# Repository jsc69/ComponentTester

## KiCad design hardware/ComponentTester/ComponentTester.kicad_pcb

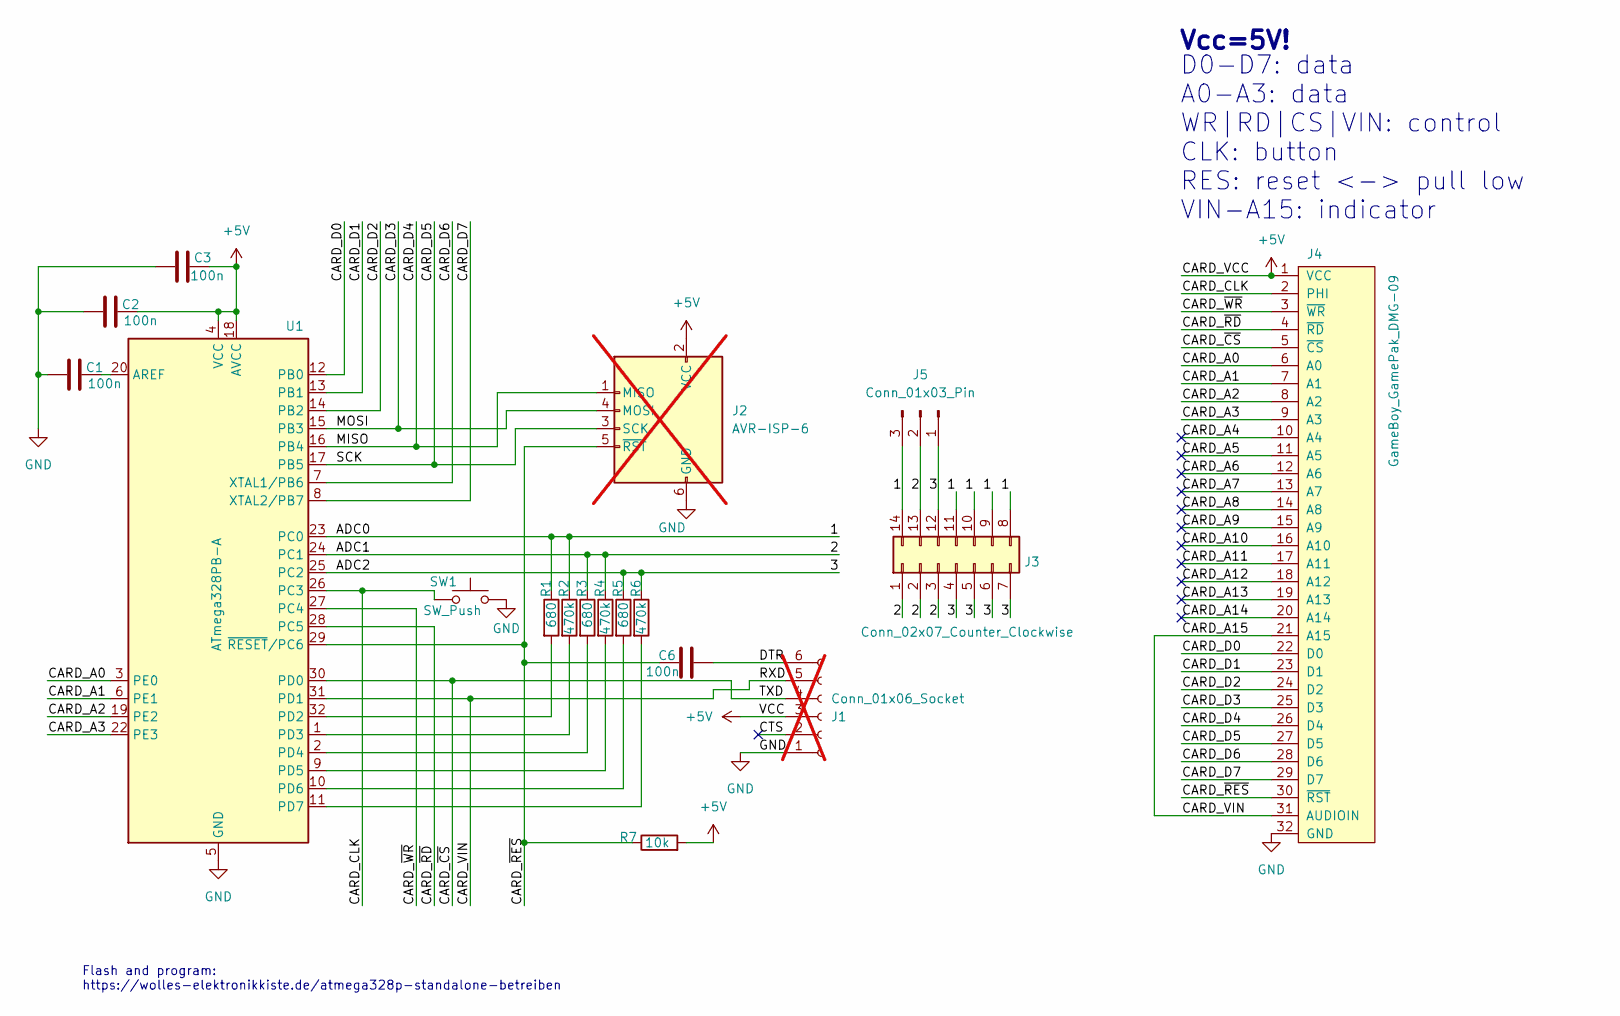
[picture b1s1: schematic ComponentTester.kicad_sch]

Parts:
C1, C2, C3, C6: 100n; C_0805_2012Metric
J1: Conn_01x06_Socket; PinHeader_1x06_P2.54mm_Vertical; not fitted
J2: AVR-ISP-6; PinHeader_2x03_P2.54mm_Vertical; not fitted
J3: Conn_02x07_Counter_Clockwise; DIP_Socket-14_W4.3mm_W5.08mm_W7.62mm_W10.16mm_W10.9mm_3M_21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
J4: GameBoy_GamePak_DMG-09; GameBoy_GamePak_DMG-09_P1.50mm_Edge
J5: Conn_01x03_Pin; Component_Testpad
R1, R3, R5: 680; R_0805_2012Metric
R2, R4, R6: 470k; R_0805_2012Metric
R7: 10k; R_0805_2012Metric
SW1: SW_Push; SW_Push_1P1T_NO_CK_KMR2
U1: ATmega328PB-A; TQFP-32_7x7mm_P0.8mm

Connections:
+5V: C2.1, C3.1, J1.3, J2.2 (VCC), J4.1 (VCC), R7.2, U1.4 (VCC), U1.18 (AVCC)
/1: J3.8, J3.9, J3.10, J3.11, J3.14, J5.3, R1.1, R2.1, U1.23 (PC0)
/2: J3.1, J3.2, J3.3, J3.13, J5.2, R3.1, R4.1, U1.24 (PC1)
/3: J3.4, J3.5, J3.6, J3.7, J3.12, J5.1, R5.1, R6.1, U1.25 (PC2)
/CARD_A0: J4.6 (A0), U1.3 (PE0)
/CARD_A1: J4.7 (A1), U1.6 (PE1)
/CARD_A2: J4.8 (A2), U1.19 (PE2)
/CARD_A3: J4.9 (A3), U1.22 (PE3)
/CARD_A4: J4.10 (A4)
/CARD_A5: J4.11 (A5)
/CARD_A6: J4.12 (A6)
/CARD_A7: J4.13 (A7)
/CARD_A8: J4.14 (A8)
/CARD_A9: J4.15 (A9)
/CARD_A10: J4.16 (A10)
/CARD_A11: J4.17 (A11)
/CARD_A12: J4.18 (A12)
/CARD_A13: J4.19 (A13)
/CARD_A14: J4.20 (A14)
/CARD_A15: J1.5, J4.21 (A15), J4.31 (AUDIOIN), U1.31 (PD1)
/CARD_CLK: J4.2 (PHI), SW1.1, U1.26 (PC3)
/CARD_D0: J4.22 (D0), U1.12 (PB0)
/CARD_D1: J4.23 (D1), U1.13 (PB1)
/CARD_D2: J4.24 (D2), U1.14 (PB2)
/CARD_D3: J2.4 (MOSI), J4.25 (D3), U1.15 (PB3)
/CARD_D4: J2.1 (MISO), J4.26 (D4), U1.16 (PB4)
/CARD_D5: J2.3 (SCK), J4.27 (D5), U1.17 (PB5)
/CARD_D6: J4.28 (D6), U1.7 (XTAL1/PB6)
/CARD_D7: J4.29 (D7), U1.8 (XTAL2/PB7)
/CARD_~CS: J1.4, J4.5 (~CS), U1.30 (PD0)
/CARD_~RD: J4.4 (~RD), U1.28 (PC5)
/CARD_~RES: C6.2, J2.5 (~RST), J4.30 (~RST), R7.1, U1.29 (~RESET/PC6)
/CARD_~WR: J4.3 (~WR), U1.27 (PC4)
/CTS: J1.2
/DTR: C6.1, J1.6
GND: C1.2, C2.2, C3.2, J1.1, J2.6 (GND), J4.32 (GND), SW1.2, U1.5 (GND), U1.21 (GND)
unnamed: C1.1, U1.20 (AREF)
unnamed: R1.2, U1.32 (PD2)
unnamed: R2.2, U1.1 (PD3)
unnamed: R3.2, U1.2 (PD4)
unnamed: R4.2, U1.9 (PD5)
unnamed: R5.2, U1.10 (PD6)
unnamed: R6.2, U1.11 (PD7)

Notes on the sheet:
Flash and program: https://wolles-elektronikkiste.de/atmega328p-standalone-betreiben
Vcc=5V!
D0-D7: data A0-A3: data WR|RD|CS|VIN: control CLK: button RES: reset <-> pull low VIN-A15: indicator

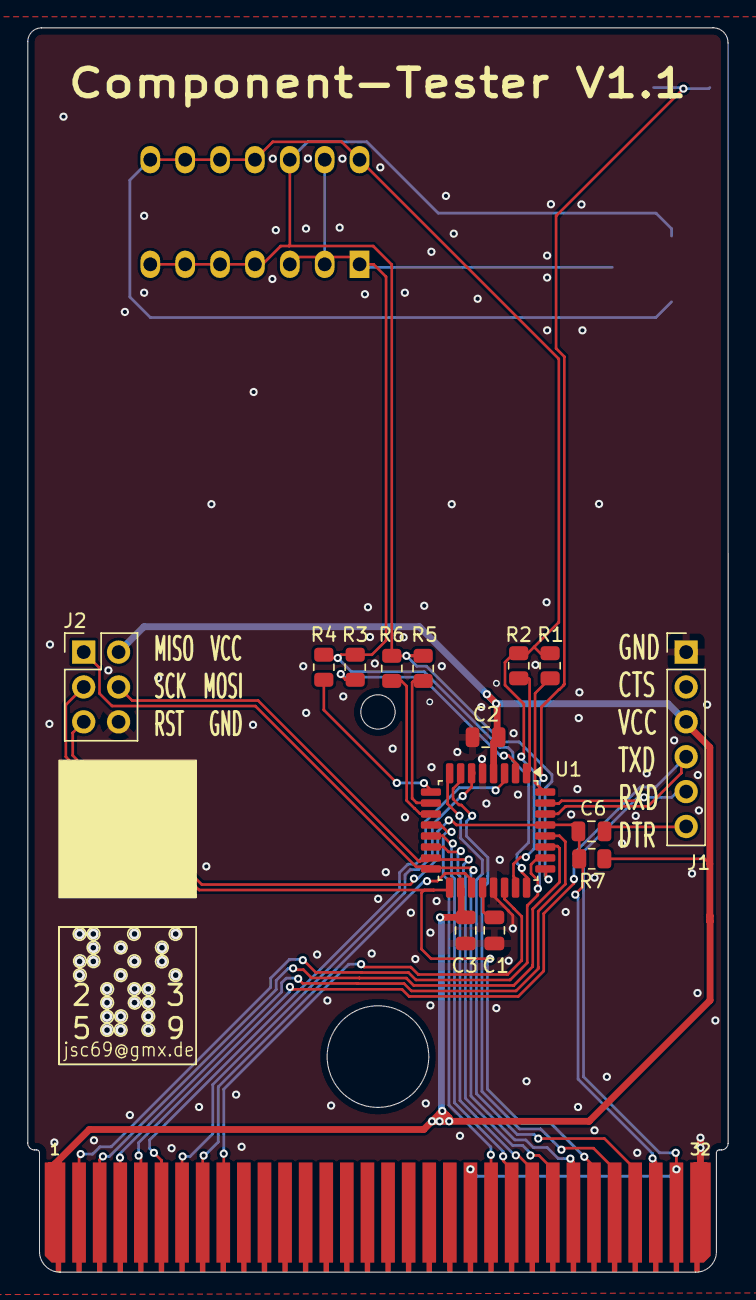
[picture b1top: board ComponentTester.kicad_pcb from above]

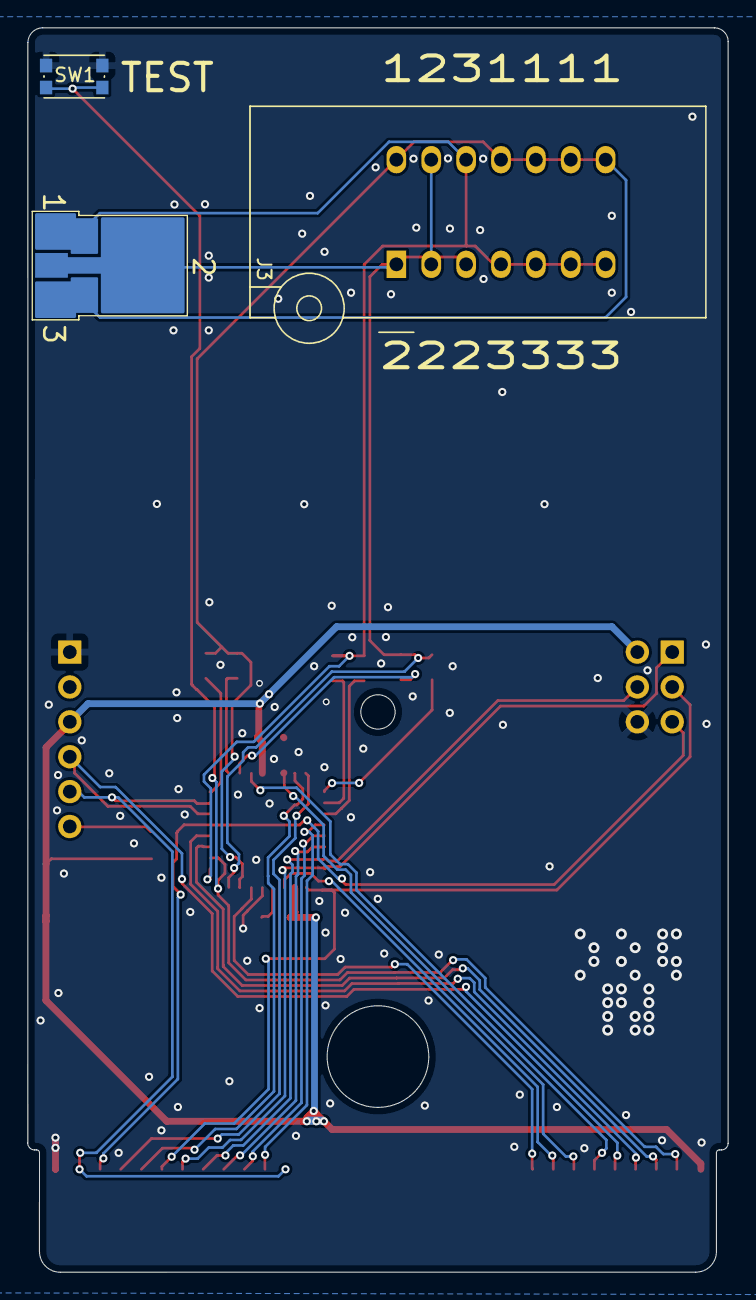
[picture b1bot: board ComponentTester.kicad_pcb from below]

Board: 2 copper layers, 51.0 x 90.6 mm, 18 parts (3 on the bottom side), 31 nets.

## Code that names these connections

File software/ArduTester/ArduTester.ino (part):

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    - pin 4: Rl3 680R (test pin 3)
    - pin 5: Rh3 470k (test pin 3)
*/
  // ATmega328PB-Platine: Widerstände an PORTD (PD2-PD7) statt PORTB
  // Original-Hardware (Arduino Uno): PORTB
  #define R_PORT                PORTD            //Port data register
  #define R_DDR                 DDRD             //Port data direction register
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const unsigned int Inductor_table[]  = {4481, 3923, 3476, 3110, 2804, 2544, 2321, 2128, 1958, 1807, 1673, 1552, 1443, 1343, 1252, 1169, 1091, 1020, 953, 890, 831, 775, 721, 670, 621, 574, 527, 481, 434, 386, 334, 271};

//Bitmasks for Rl probe resistors based on probe ID
  // ATmega328PB-Platine: Rl an PD2/PD4/PD6, Rh an PD3/PD5/PD7
  // (Original Arduino Uno: Rl an PB0/PB2/PB4, Rh an PB1/PB3/PB5)
  const unsigned char Rl_table[] = {(1 << 2), (1 << 4), (1 << 6)};  // PD2, PD4, PD6
  #define RL_MASK(tp)  (Rl_table[tp])
  #define RH_MASK(tp)  (Rl_table[tp] << 1)

  // Bus-Defines für ESP32-Schnittstelle
  #define BUS_ID_DDR    DDRE    // PE0-PE3 fuer ID (CARD_A0-A3)
  #define BUS_ID_PORT   PORTE
  #define BUS_DATA_DDR  DDRB    // PB0-PB7 fuer Daten (CARD_D0-D7)
  #define BUS_DATA_PORT PORTB

  uint8_t ValueCounter = 0;    // Zaehler fuer VAL1..VAL4 in DisplayValue()
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// ================================================================
// FOR_BRUTZELBOY: Bus-Kommunikation und Kommandoempfang
//
// Nur 2 Steuerpins — CS (PD0) wird nicht verwendet:
//   PC4 (CARD_WR) — ATmega → ESP32: Frame-Strobe / Bereit-ACK
//   PC5 (CARD_RD) — ESP32  → ATmega: Frame-ACK / Kommando-Trigger
//
// ATmega sendet Frame:
//   ① ID + Data auf PE0-3 / PB0-7 anlegen
//   ② WR = HIGH  ("Frame liegt an")
//   ③ warten auf RD = HIGH vom ESP32 (ACK, max. BB_ACK_TIMEOUT_US)
//   ④ WR = LOW   ("Übertragung fertig")
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//   ⑤ ATmega liest PINE & PINB, setzt WR = LOW ("gelesen")
//   ⑥ ESP32 sieht WR = LOW → setzt RD = LOW, gibt Bus frei
//
// Kommando-Tabelle (PE0-PE3):
//   0x0  NOP          - nichts tun
//   0x1  START_TEST   - neuen Bauteiltest starten
//   0x2  FREQ_METER   - Frequenzmessung (STUB)
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#define BB_HANDSHAKE_PIN   PINC
#define BB_HANDSHAKE_DDR   DDRC
#define BB_HANDSHAKE_PORT  PORTC
#define BB_WR_BIT   PC4    // ATmega → ESP32: Frame-Strobe / Bereit-ACK
#define BB_RD_BIT   PC5    // ESP32  → ATmega: Frame-ACK / Kommando-Trigger

#define BB_BTN_PIN  PINC
#define BB_BTN_DDR  DDRC
#define BB_BTN_BIT  PC3    // Taster: GND = gedrückt (low-active)

// PORTC-Bits die nie durch ADC_DDR/ADC_PORT-Zuweisungen überschrieben werden dürfen
#define BB_PORTC_PRESERVE  ((1<<BB_WR_BIT)|(1<<BB_RD_BIT)|(1<<BB_BTN_BIT))  // 0x38
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
// Handshake initialisieren (in setup() aufrufen)
void bbHandshakeInit() {
  BB_HANDSHAKE_PORT |=  (1 << BB_WR_BIT);   // PC4 HIGH (idle) — vor DDR!
  BB_HANDSHAKE_PORT |=  (1 << BB_RD_BIT);   // PC5 Pull-up (RD idle = HIGH)
  BB_HANDSHAKE_DDR  |=  (1 << BB_WR_BIT);   // PC4 = Ausgang
  BB_HANDSHAKE_DDR  &= ~(1 << BB_RD_BIT);   // PC5 = Eingang
  BB_BTN_DDR &= ~(1 << BB_BTN_BIT);  // PC3 = Eingang
  PORTC      |=  (1 << BB_BTN_BIT);  // PC3 Pull-up
}

// Warte auf Ende der Kommunikation (BUS_IDLE)
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
// Einen Frame senden mit Handshake.
// Gibt true zurück wenn ESP32 ACK gegeben hat, false bei Timeout.
// PC4 (WR) als Ausgang sicherstellen — wird durch ADC_DDR-Zuweisungen gelöscht
bool sendToEsp(uint8_t id, uint8_t data) {
  BB_HANDSHAKE_DDR |= (1 << BB_WR_BIT);

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}

// Kommando vom ESP32 empfangen.
// Wird in loop() aufgerufen wenn RD (PC5) = HIGH erkannt wurde.
// Gibt true zurück wenn ein gültiges Kommando (cmd != 0x00) gelesen wurde.
bool checkBrutzelBoyCommand(uint8_t &cmd, uint8_t &param) {
  // Bus als Eingang mit Pull-ups
  DDRB = 0x00;   DDRE = 0x00;
  PORTB = 0xFF;  PORTE = 0xFF;
  BUS_ID_DDR  &= ~0x0F;
  SetADCHiz();   // PC0-PC2 als Eingang — lässt PC4 (WR) unberührt

  // Schritt 1: WR=LOW — "ATmega bereit zum Lesen"
  BB_HANDSHAKE_PORT &= ~(1 << BB_WR_BIT);
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  //Setup 
  ADCSRA = (1 << ADEN) | ADC_CLOCK_DIV;          //Enable ADC and set clock divider 
  MCUSR &= ~(1 << WDRF);                         //Reset watchdog flag 
  DIDR0 = 0b00010111;                            // Bit 5 (ADC5/PC5 = RD) nicht deaktivieren                           
  wdt_disable();                                 //Disable watchdog 

  //Default offsets and values
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//PWM tool
void PWM_Tool(unsigned int Frequency)
{
  //Use probe #2 (PB2, OC1B) as PWM output and probe #1 + probe #3 as ground - Freqency in Hz
  byte                        Test = 1;          //Loop control and user feedback 
  byte                        Ratio;             //PWM ratio 
  byte                        Prescaler;         //Timer prescaler 
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  }
  //Clean up
  TCCR1B = 0;                                    //Disable timer
  TCCR1A = 0;                                    //Reset flags (also frees PB2)
  R_DDR = 0;                                     //Set HiZ mode
  Config.SleepMode = SLEEP_MODE_PWR_SAVE;        //Reset sleep mode to default
}
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
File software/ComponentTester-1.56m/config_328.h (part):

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#define BRUTZEL_PORT     PORTC
#define BRUTZEL_DDR      DDRC
#define BRUTZEL_PIN      PINC
#define BRUTZEL_WR       PC4    /* Ausgang: ATmega zeigt G�ltigkeit an */
#define BRUTZEL_RD       PC5    /* Eingang: ESP32 ACK / Sende-Wunsch */

#define BUTTON_PORT      PORTC
#define BUTTON_DDR       DDRC
#define BUTTON_PIN       PINC
#define TEST_BUTTON      PC3         /* Dein Knopf an PC3 */
/* --- Test Button Setup für PC3 --- */
#define TEST_KEY_PORT    PORTC    /* Port für die Pull-Up Steuerung */
#define TEST_KEY_DDR     DDRC     /* Datenrichtungsregister */
#define TEST_KEY_PIN     PINC     /* Register zum Einlesen des Zustands */
#define TEST_KEY         PC3      /* Die Bit-Position (Pin 3) */

/* --- Batterie-Messung --- */
/* Da kein Pin frei ist, messen wir die interne Referenzspannung */
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#define LCD_PORT         PORTD          /* port data register */
#define LCD_DDR          DDRD           /* port data direction register */
#define LCD_DB_STD                      /* use standard pins 0-3 for DB4-7 */
#define LCD_DB4          PD0            /* port pin used for DB4 */
#define LCD_DB5          PD1            /* port pin used for DB5 */
#define LCD_DB6          PD2            /* port pin used for DB6 */
#define LCD_DB7          PD3            /* port pin used for DB7 */
#define LCD_RS           PD4            /* port pin used for RS */
#define LCD_EN1          PD5            /* port pin used for E */
/* display settings */
#define LCD_CHAR_X       16             /* characters per line */
#define LCD_CHAR_Y       2              /* number of lines */
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#define I2C_PORT         PORTD          /* I2C port data register */
#define I2C_DDR          DDRD           /* I2C port data direction register */
#define I2C_PIN          PIND           /* I2C port input pins register */
#define I2C_SDA          PD0            /* port pin used for SDA */
#define I2C_SCL          PD1            /* port pin used for SCL */
#endif


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/* control and data lines */
#define LCD_PORT         PORTD          /* port data register */
#define LCD_DDR          DDRD           /* port data direction register */
#define LCD_RES          PD4            /* port pin used for /RESX (optional) */
#define LCD_CS           PD5            /* port pin used for /CSX (optional) */
#define LCD_DC           PD3            /* port pin used for D/CX */
#define LCD_SCL          PD2            /* port pin used for SCL */
#define LCD_SDA          PD1            /* port pin used for SDA/SDIO */
/* display settings */
#define LCD_DOTS_X       128            /* number of horizontal dots */
#define LCD_DOTS_Y       128            /* number of vertical dots */
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/* control and data lines */
#define LCD_PORT         PORTD          /* port data register */
#define LCD_DDR          DDRD           /* port data direction register */
#define LCD_RES          PD4            /* port pin used for /RES (optional) */
#define LCD_CS           PD5            /* port pin used for /CS (optional) */
#define LCD_DC           PD3            /* port pin used for D/C */
#define LCD_SCK          PD2            /* port pin used for SCK */
#define LCD_SDI          PD1            /* port pin used for SDI (data input) */
//#define LCD_SDO          PD0            /* port pin used for SDO (data output) */
/* display settings */
#define LCD_DOTS_X       320            /* number of horizontal dots */
#define LCD_DOTS_Y       240            /* number of vertical dots */
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/* control and data lines */
#define LCD_PORT         PORTD          /* port data register */
#define LCD_DDR          DDRD           /* port data direction register */
#define LCD_RES          PD4            /* port pin used for /RES (optional) */
#define LCD_SCE          PD5            /* port pin used for /SCE (optional) */
#define LCD_DC           PD3            /* port pin used for D/C */
#define LCD_SCLK         PD2            /* port pin used for SCLK */
#define LCD_SDIN         PD1            /* port pin used for SDIN (data input) */
/* display settings */
#define LCD_DOTS_X       84             /* number of horizontal dots */
#define LCD_DOTS_Y       48             /* number of vertical dots */
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/* control and data lines */
#define LCD_PORT         PORTD          /* port data register */
#define LCD_DDR          DDRD           /* port data direction register */
#define LCD_RESET        PD4            /* port pin used for /RES */
#define LCD_CS           PD5            /* port pin used for /CS (optional) */
#define LCD_SCLK         PD2            /* port pin used for SCLK */
#define LCD_SDIN         PD1            /* port pin used for SDIN (data input) */
/* display settings */
#define LCD_DOTS_X       96             /* number of horizontal dots */
#define LCD_DOTS_Y       65             /* number of vertical dots */
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/* control and data lines */
#define LCD_PORT         PORTD          /* port data register */
#define LCD_DDR          DDRD           /* port data direction register */
#define LCD_RESET        PD4            /* port pin used for /RES (optional) */
#define LCD_CS           PD5            /* port pin used for /CS (optional) */
#define LCD_A0           PD3            /* port pin used for A0 */
#define LCD_SCL          PD2            /* port pin used for SCL */
#define LCD_SI           PD1            /* port pin used for SI (data input) */
/* display settings */
#define LCD_DOTS_X       128            /* number of horizontal dots */
#define LCD_DOTS_Y       64             /* number of vertical dots */
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/* control and data lines */
#define LCD_PORT         PORTD          /* port data register */
#define LCD_DDR          DDRD           /* port data direction register */
#define LCD_RESET        PD4            /* port pin used for /RES (optional) */
#define LCD_CS           PD5            /* port pin used for /CS (optional) */
#define LCD_SCL          PD2            /* port pin used for SCL */
#define LCD_SI           PD1            /* port pin used for SI (data input) */
/* display settings */
#define LCD_DOTS_X       128            /* number of horizontal dots */
#define LCD_DOTS_Y       64             /* number of vertical dots */
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/* control lines */
#define LCD_PORT         PORTD          /* port data register */
#define LCD_DDR          DDRD           /* port data direction register */
//#define LCD_RESET        PD4            /* port pin used for /RES (optional) */
/* display settings */
#define LCD_DOTS_X       128            /* number of horizontal dots */
#define LCD_DOTS_Y       64             /* number of vertical dots */
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#define I2C_PORT         PORTD          /* I2C port data register */
#define I2C_DDR          DDRD           /* I2C port data direction register */
#define I2C_PIN          PIND           /* I2C port input pins register */
#define I2C_SDA          PD0            /* port pin used for SDA */
#define I2C_SCL          PD1            /* port pin used for SCL */
#endif


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/* control and data lines */
#define LCD_PORT         PORTD          /* port data register */
#define LCD_DDR          DDRD           /* port data direction register */
#define LCD_RESET        PD4            /* port pin used for /RES (optional) */
#define LCD_CS           PD5            /* port pin used for /CS (optional) */
#define LCD_DC           PD3            /* port pin used for D/C */
#define LCD_SCLK         PD2            /* port pin used for SCLK */
#define LCD_SDIN         PD1            /* port pin used for SDIN (data input) */
/* display settings */
#define LCD_DOTS_X       128            /* number of horizontal dots */
#define LCD_DOTS_Y       64             /* number of vertical dots */
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/* control and data lines */
#define LCD_PORT         PORTD          /* port data register */
#define LCD_DDR          DDRD           /* port data direction register */
#define LCD_RESET        PD4            /* port pin used for /RES (optional) */
#define LCD_CS           PD5            /* port pin used for /CS (optional) */
#define LCD_SCLK         PD2            /* port pin used for SCLK */
#define LCD_SDIN         PD1            /* port pin used for SDIN (data input) */
/* display settings */
#define LCD_DOTS_X       128            /* number of horizontal dots */
#define LCD_DOTS_Y       64             /* number of vertical dots */
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/* control lines */
#define LCD_PORT         PORTD          /* port data register */
#define LCD_DDR          DDRD           /* port data direction register */
#define LCD_RESET        PD4            /* port pin used for /RES (optional) */
/* display settings */
#define LCD_DOTS_X       128            /* number of horizontal dots */
#define LCD_DOTS_Y       64             /* number of vertical dots */
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#define I2C_PORT         PORTD          /* I2C port data register */
#define I2C_DDR          DDRD           /* I2C port data direction register */
#define I2C_PIN          PIND           /* I2C port input pins register */
#define I2C_SDA          PD0            /* port pin used for SDA */
#define I2C_SCL          PD1            /* port pin used for SCL */
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
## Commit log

2025-09-21 use ADC6 + ADC7
2025-09-21 remove ext. crystal
2025-09-21 clean up
2025-10-31 some work
2025-11-30 replace ATmega328P with ATmegaPB
2026-03-12 hardware changes
2026-03-12 renaming
2026-03-14 fix workflow for test start
2026-03-14 unstable fix
2026-03-15 further fix of communication
2026-03-16 looks like a fix for the handshake problem
2026-03-16 clean ups
2026-03-16 A-Button fix
2026-03-16 correction of tps and values

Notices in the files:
software/ComponentTester-1.56m/config_328.h:
(c) 2012-2024 by Markus Reschke
